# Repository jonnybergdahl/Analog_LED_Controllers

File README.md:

# Analog_LED_Controller

This repository contains 2 versions of a two channel analog LED controller. 

> Note: This is only suitable for LED lights powered by a fixed voltage, such as plant lights and LED strips. It does not work with raw LED's that need a constant current/voltage driver. 

One version is for 5V USB connected lights, the "USB version", and the other version is for 5-24V lights, the "Power jack version" using standard 5.5/2.1 mm power jacks. They are based on an ESP32-PICO-MINI-2 module, and I use it with ESPHome firmware to publish the lights to Home Assistant. Inside of Home Assistant you can dim the lights and turn them on or off. Both have a power jack input for power, make sure to use a power supply with center positive.

> Note: The boards have reverse power input protection for the internal circuitry only. The LED's outputs are protected by resettable fuses. This should not pose any problems as long as you only power LED's, since they are themselves diodes and thus already protected from reverse power.

The input power jack is rated for maximum 5A so depending on input voltage the max combined power is:
 - 5V: 25W
 - 12V: 60W
 - 24V: 120W

### USB version

### Power jack version

The gerber files for PCB manufacturing are located in the [gerber folder](gerber/).

I highly recommend you order a stencil together with the PCB, as the ESP32 module only exposes tiny pads on the bottom of the module and it is hard to get the correct amount of solder paste without one.

PCB design files are available in [EAGLE format](pcb/).

The Schematic is also available in PDF Format, [USB version](https://github.com/jonnybergdahl/Project_Analog_LED_Controllers/blob/main/pcb/5V_Analog_Controller.pdf) and [Power jack version](https://github.com/jonnybergdahl/Project_Analog_LED_Controllers/blob/main/pcb/12V_Analog_Controller.pdf).

## Parts needed

BOM file are located here: 
 - [USB version](pcb/USB_Analog_Controller.csv)
 - [Power jack version](pcb/USB_Analog_Controller%2024V.csv).

> Note: There is space for 2 PTC's per channel in case you need more current than a single PTC can handle. Make sure to use PTC's rated for the voltage _and_ current you want. The JK-SMD300L-24 in the BOM are rated for max 24V and a hold current of 3 ampere.

### USB version

### Power jack version

See the [BOM file](pcb/LED_USB_Analog_Controller.csv) for the component list.

## Enclosure

The enclosure files are located in the [enclosure folder](enclosure/). There are two `3mf` files for 3D printing for each device, and I also added the original _Fusion 360_ design files in case you need to make modifications.

## Assembly

 Start by soldering all SMD parts onto the PCB. I used a hot plate for resoldering, but a hot air soldering station will also work. Continue by using a soldering iron to solder the connectors. For the USB version, Cut an existing USB cable or do like me and solder up your own, and screw plus and minus to the screw terminals (Depending on the power usage of the lights, you may need thicker cables than normal USB cables, that is why I make my own power only ones). 

The enclosure is press fit so does not need any extra hardware or tools.

## Programming

Create a new device in _ESPHome_ and replace the `yaml` with the contents of [the yaml code here](firmware/led1.yaml). Change `name` and `friendly_name` as needed.

The actual programming is done by using a standard FT232 serial board connected to the programming header. If you don't own a FT232 adapter, you can use other types of serial adapters by hooking up `GND`, `TX` and `RX` like this.

Insert the programmer and short the `BOOT` header. It can be done by soldering a temporary lead between the pads (I just insert tweezers into the pads). Apply power and it is ready for programming.

In _EspHome_,  click `Install` - `Manual download` - `Modern format`. _EspHome_ will compile the code and after couple of minutes the firmware file will be downloaded. 

Open the [ESPHome programming page](https://web.esphome.io/) and click `CONNECT`. Select the FT232 serial port and click `Connect`. Select `Install` and then click `Select file`. Select the file downloaded in the previous step and then click `Install`. The install will now proceed.

When install is finished, just remove the FT232 board and `BOOT` jumper, disconnect and connect power, and after a while Home Assistant will autodetect it. Just add the device as usual and you will get a device with the following entities in Home Assistant.

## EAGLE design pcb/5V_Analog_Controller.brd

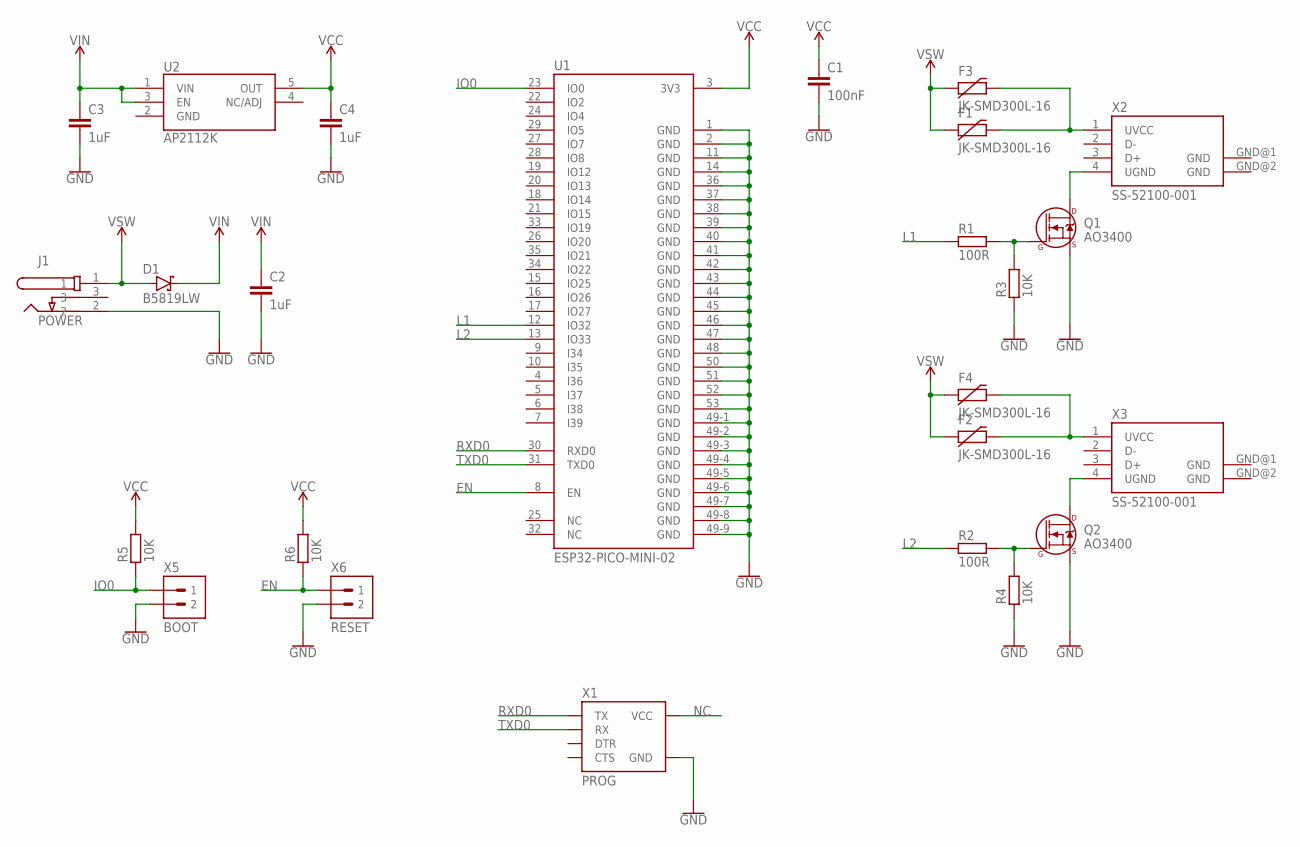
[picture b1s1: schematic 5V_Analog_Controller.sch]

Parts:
C1: 100nF; C0603
C2, C3, C4: 1uF; C0603
D1: B5819LW; SOD-123
F1, F2, F3, F4: JK-SMD300L-16; JK-SMD300
J1: POWER; XKB-DC-005-5A-2.0
Q1, Q2: AO3400; SOT23-3
R1, R2: 100R; R0603
R3, R4, R5, R6: 10K; R0603
U1: ESP32-PICO-MINI-02
U2: AP2112K; SOT23-5
X1: PROG; FTDI232-1X06
X2, X3: SS-52100-001; USB-A-SS-52100-001
X5: BOOT; 1X02-2.54
X6: RESET; 1X02-2.54

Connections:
EN: R6.1, U1.8 (EN), X6.1
GND: C1.2, C2.2, C3.2, C4.2, J1.2, Q1.2 (S), Q2.2 (S), R3.1, R4.1, U1.1 (GND), U1.2 (GND), U1.11 (GND), U1.14 (GND), U1.36 (GND), U1.37 (GND), U1.38 (GND), U1.39 (GND), U1.40 (GND), U1.41 (GND), U1.42 (GND), U1.43 (GND), U1.44 (GND), U1.45 (GND), U1.46 (GND), U1.47 (GND), U1.48 (GND), U1.49-1 (GND), U1.49-2 (GND), U1.49-3 (GND), U1.49-4 (GND), U1.49-5 (GND), U1.49-6 (GND), U1.49-7 (GND), U1.49-8 (GND), U1.49-9 (GND), U1.50 (GND), U1.51 (GND), U1.52 (GND), U1.53 (GND), U2.2 (GND), X1.GND, X5.2, X6.2
IO0: R5.1, U1.23 (IO0), X5.1
L1: R1.1, U1.12 (IO32)
L2: R2.1, U1.13 (IO33)
unnamed: Q1.3 (D), X2.4 (UGND)
unnamed: Q2.3 (D), X3.4 (UGND)
unnamed: Q2.1 (G), R2.2, R4.2
unnamed: Q1.1 (G), R1.2, R3.2
unnamed: F1.B (2), F3.B (2), X2.1 (UVCC)
unnamed: F2.B (2), F4.B (2), X3.1 (UVCC)
NC: X1.VCC
RXD0: U1.30 (RXD0), X1.TX
TXD0: U1.31 (TXD0), X1.RX
VCC: C1.1, C4.1, R5.2, R6.2, U1.3 (3V3), U2.5 (OUT)
VIN: C2.1, C3.1, D1.C, U2.1 (VIN), U2.3 (EN)
VSW: D1.A, F1.A (1), F2.A (1), F3.A (1), F4.A (1), J1.1

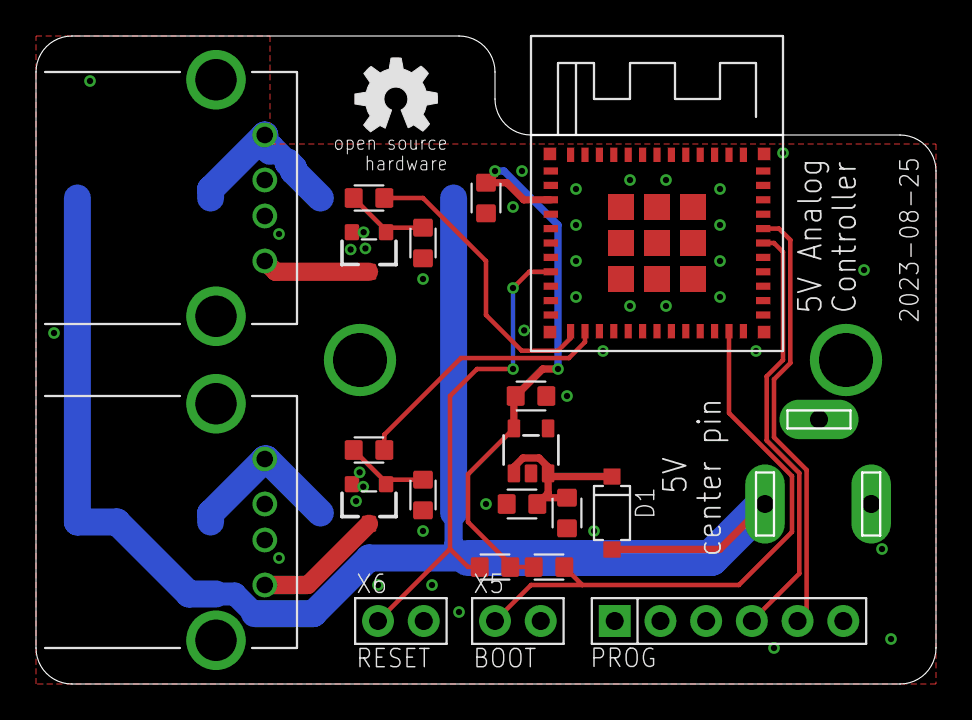
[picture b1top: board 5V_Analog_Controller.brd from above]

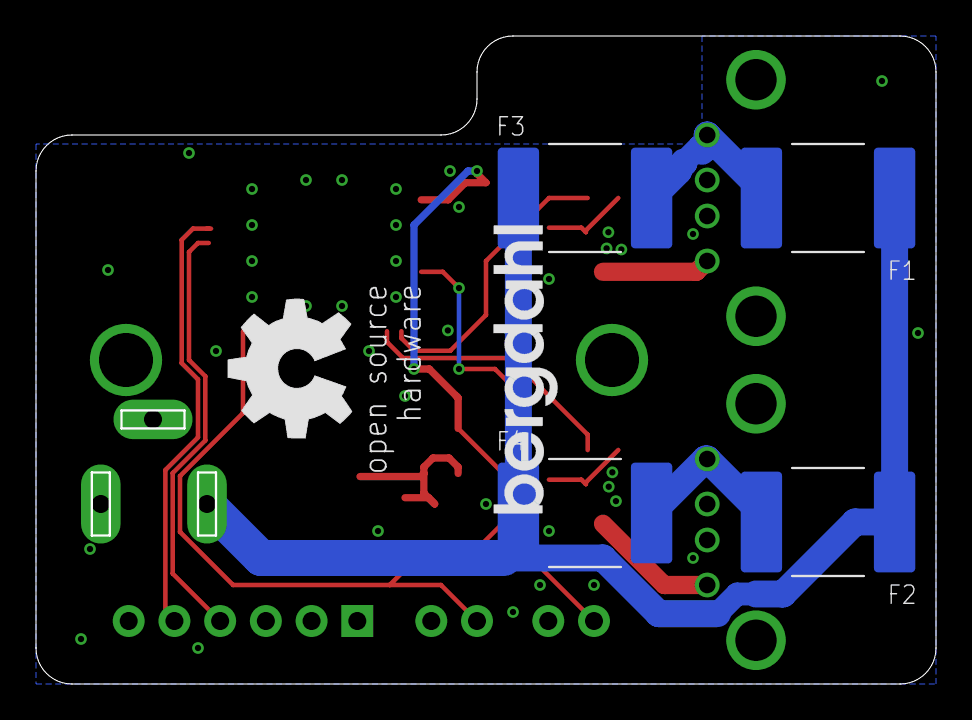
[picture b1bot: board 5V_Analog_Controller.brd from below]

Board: 2 copper layers, 49.9 x 35.9 mm, 28 parts (4 on the bottom side), 16 nets.

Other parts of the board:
U$1: BERGDAHL-20MM-BPLACE
U$2: OSHW-8MM-BPLACE
U$3: OSHW-5MM-TPLACE

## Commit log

2023-06-03 Initial version
2023-07-17 Revision 2023-07-17
2023-07-27 Added PTC fuse
2023-08-03 Final PCB version
2023-08-03 Spelling
2023-08-03 Fix spelling and yaml indentation
2023-08-03 Added instructions for non FT232 adapter hookup
2023-08-04 Revision 2023-08-04 Switch power connector Add PDF file Cleanup old PCB files
2023-08-04 Added links to EAGLE and PDF files
2023-08-09 Add 5-24V version
2023-08-09 Add missing drill file
2023-08-14 Change connector on24V PCB Cosmetic fixes on 24V PCB
2023-08-20 Major renaming work
2023-08-20 Moved repo to better named location
2023-08-20 Revert "Major renaming work"
    This reverts commit 9d1dc4bb5ff05094a4a5c98072b5adfe142c2125.
2023-08-20 Re-add assets
2023-08-20 Moved all files
2023-08-20 Fix snap issue
2023-08-24 Switch to input power jack
2023-08-24 Add reverse power protection for internal circuits
2023-08-24 Update enclosure files for power jack cutout
2023-08-25 Add second PTC footprint
2023-08-25 Increased combined current capability
2023-08-25 Increase current capablity
